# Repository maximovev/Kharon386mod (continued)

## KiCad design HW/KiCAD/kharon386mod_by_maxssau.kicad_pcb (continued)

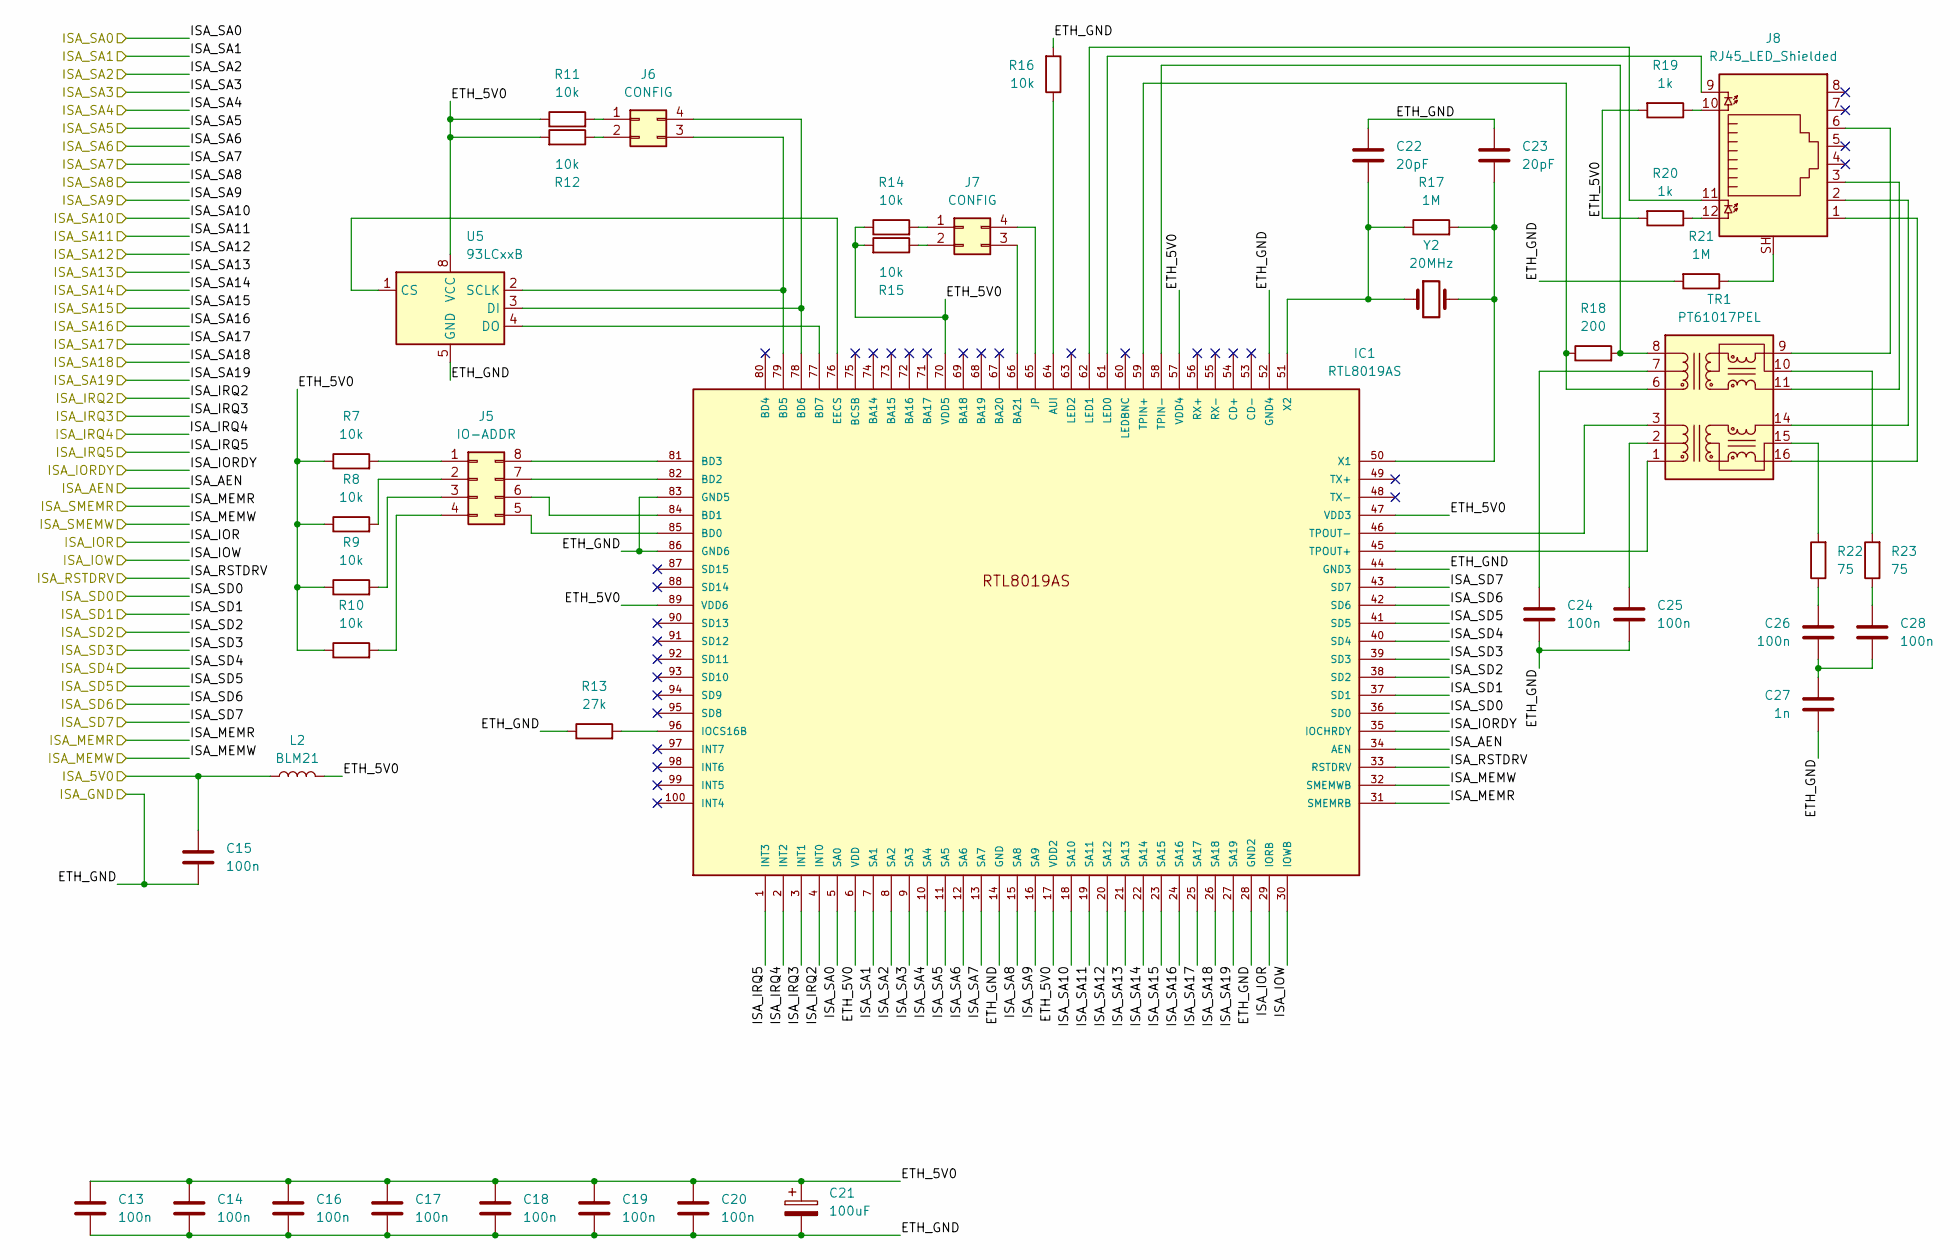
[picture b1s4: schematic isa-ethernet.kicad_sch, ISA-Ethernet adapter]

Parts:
C13, C14, C15, C16, C17, C18, C19, C20, C24, C25, C26, C28: 100n; C_0805_2012Metric_Pad1.18x1.45mm_HandSolder
C21: 100uF; CP_Elec_6.3x5.9
C22, C23: 20pF; C_0805_2012Metric_Pad1.18x1.45mm_HandSolder
C27: 1n; C_0805_2012Metric_Pad1.18x1.45mm_HandSolder
IC1: RTL8019AS
J5: IO-ADDR; PinHeader_2x04_P2.54mm_Vertical
J6, J7: CONFIG; PinHeader_2x02_P2.54mm_Vertical
J8: RJ45_LED_Shielded; RJ45_Cetus_J1B1211CCD_Horizontal
L2: BLM21; L_1210_3225Metric_Pad1.42x2.65mm_HandSolder
R7, R8, R9, R10, R11, R12, R14, R15, R16: 10k; R_0805_2012Metric_Pad1.20x1.40mm_HandSolder
R13: 27k; R_0805_2012Metric_Pad1.20x1.40mm_HandSolder
R17, R21: 1M; R_0805_2012Metric_Pad1.20x1.40mm_HandSolder
R18: 200; R_0805_2012Metric_Pad1.20x1.40mm_HandSolder
R19, R20: 1k; R_0805_2012Metric_Pad1.20x1.40mm_HandSolder
R22, R23: 75; R_0805_2012Metric_Pad1.20x1.40mm_HandSolder
TR1: PT61017PEL; Transformer_Ethernet_Bourns_PT61017PEL
U5: 93LCxxB; SOIC-8_3.9x4.9mm_P1.27mm
Y2: 20MHz; Crystal_HC49-U_Vertical

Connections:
/B_ISA_5V0: C15.1, L2.1; also elsewhere on the board
/B_ISA_A0: IC1.5 (SA0); also elsewhere on the board
/B_ISA_A1: IC1.7 (SA1); also elsewhere on the board
/B_ISA_A2: IC1.8 (SA2); also elsewhere on the board
/B_ISA_A3: IC1.9 (SA3); also elsewhere on the board
/B_ISA_A4: IC1.10 (SA4); also elsewhere on the board
/B_ISA_A5: IC1.11 (SA5); also elsewhere on the board
/B_ISA_A6: IC1.12 (SA6); also elsewhere on the board
/B_ISA_A7: IC1.13 (SA7); also elsewhere on the board
/B_ISA_A8: IC1.15 (SA8); also elsewhere on the board
/B_ISA_A9: IC1.16 (SA9); also elsewhere on the board
/B_ISA_A10: IC1.18 (SA10); also elsewhere on the board
/B_ISA_A11: IC1.19 (SA11); also elsewhere on the board
/B_ISA_A12: IC1.20 (SA12); also elsewhere on the board
/B_ISA_A13: IC1.21 (SA13); also elsewhere on the board
/B_ISA_A14: IC1.22 (SA14); also elsewhere on the board
/B_ISA_A15: IC1.23 (SA15); also elsewhere on the board
/B_ISA_A16: IC1.24 (SA16); also elsewhere on the board
/B_ISA_A17: IC1.25 (SA17); also elsewhere on the board
/B_ISA_A18: IC1.26 (SA18); also elsewhere on the board
/B_ISA_A19: IC1.27 (SA19); also elsewhere on the board
/B_ISA_AEN: IC1.34 (AEN); also elsewhere on the board
/B_ISA_D0: IC1.36 (SD0); also elsewhere on the board
/B_ISA_D1: IC1.37 (SD1); also elsewhere on the board
/B_ISA_D2: IC1.38 (SD2); also elsewhere on the board
/B_ISA_D3: IC1.39 (SD3); also elsewhere on the board
/B_ISA_D4: IC1.40 (SD4); also elsewhere on the board
/B_ISA_D5: IC1.41 (SD5); also elsewhere on the board
/B_ISA_D6: IC1.42 (SD6); also elsewhere on the board
/B_ISA_D7: IC1.43 (SD7); also elsewhere on the board
/B_ISA_IOR: IC1.29 (IORB); also elsewhere on the board
/B_ISA_IORDY: IC1.35 (IOCHRDY); also elsewhere on the board
/B_ISA_IOW: IC1.30 (IOWB); also elsewhere on the board
/B_ISA_IRQ3: IC1.3 (INT1); also elsewhere on the board
/B_ISA_IRQ4: IC1.2 (INT2); also elsewhere on the board
/B_ISA_IRQ5: IC1.1 (INT3); also elsewhere on the board
/B_ISA_IRQ9: IC1.4 (INT0); also elsewhere on the board
/B_ISA_RSTDRV: IC1.33 (RSTDRV); also elsewhere on the board
/B_ISA_SMEMR: IC1.31 (SMEMRB); also elsewhere on the board
/B_ISA_SMEMW: IC1.32 (SMEMWB); also elsewhere on the board
/isa-ethernet/ETH_5V0: C13.1, C14.1, C16.1, C17.1, C18.1, C19.1, C20.1, C21.1, IC1.6 (VDD), IC1.17 (VDD2), IC1.47 (VDD3), IC1.57 (VDD4), IC1.70 (VDD5), IC1.89 (VDD6), L2.2, R7.1, R8.1, R9.1, R10.1, R11.1, R12.2, R14.1, R15.2, R19.2, R20.2, U5.8 (VCC)
GND: C13.2, C14.2, C15.2, C16.2, C17.2, C18.2, C19.2, C20.2, C21.2, C22.2, C23.2, C24.2, C25.2, C27.2, IC1.14 (GND), IC1.28 (GND2), IC1.44 (GND3), IC1.52 (GND4), IC1.83 (GND5), IC1.86 (GND6), R13.1, R16.2, R21.2, U5.5 (GND); also elsewhere on the board
unnamed: C26.1, R22.1
unnamed: C26.2, C27.1, C28.2
unnamed: C28.1, R23.1
unnamed: IC1.64 (AUI), R16.1
unnamed: IC1.66 (BA21), J7.3
unnamed: IC1.85 (BD0), J5.5
unnamed: IC1.84 (BD1), J5.6
unnamed: IC1.82 (BD2), J5.7
unnamed: IC1.81 (BD3), J5.8
unnamed: IC1.79 (BD5), J6.3, U5.2 (SCLK)
unnamed: IC1.78 (BD6), J6.4, U5.3 (DI)
unnamed: IC1.77 (BD7), U5.4 (DO)
unnamed: IC1.76 (EECS), U5.1 (CS)
unnamed: IC1.96 (IOCS16B), R13.2
unnamed: IC1.65 (JP), J7.4
unnamed: IC1.61 (LED0), J8.9
unnamed: IC1.62 (LED1), J8.11
unnamed: IC1.59 (TPIN+), R18.1, TR1.6 (RD+)
unnamed: IC1.58 (TPIN-), R18.2, TR1.8 (RD-)
unnamed: IC1.45 (TPOUT+), TR1.1 (TD+)
unnamed: IC1.46 (TPOUT-), TR1.3 (TD-)
unnamed: C23.1, IC1.50 (X1), R17.2, Y2.2
unnamed: C22.1, IC1.51 (X2), R17.1, Y2.1
unnamed: J5.1, R7.2
unnamed: J5.2, R8.2
unnamed: J5.3, R9.2
unnamed: J5.4, R10.2
unnamed: J6.1, R11.2
unnamed: J6.2, R12.1
unnamed: J7.1, R14.2
unnamed: J7.2, R15.1
unnamed: J8.10, R19.1
unnamed: J8.12, R20.1
unnamed: J8.SH, R21.1
unnamed: C24.1, TR1.7 (C_RD)
unnamed: R23.2, TR1.10 (C_RX)
unnamed: C25.1, TR1.2 (C_TD)
unnamed: R22.2, TR1.15 (C_TX)
unnamed: J8.3, TR1.11 (RX+)
unnamed: J8.6, TR1.9 (RX-)
unnamed: J8.1, TR1.16 (TX+)
unnamed: J8.2, TR1.14 (TX-)

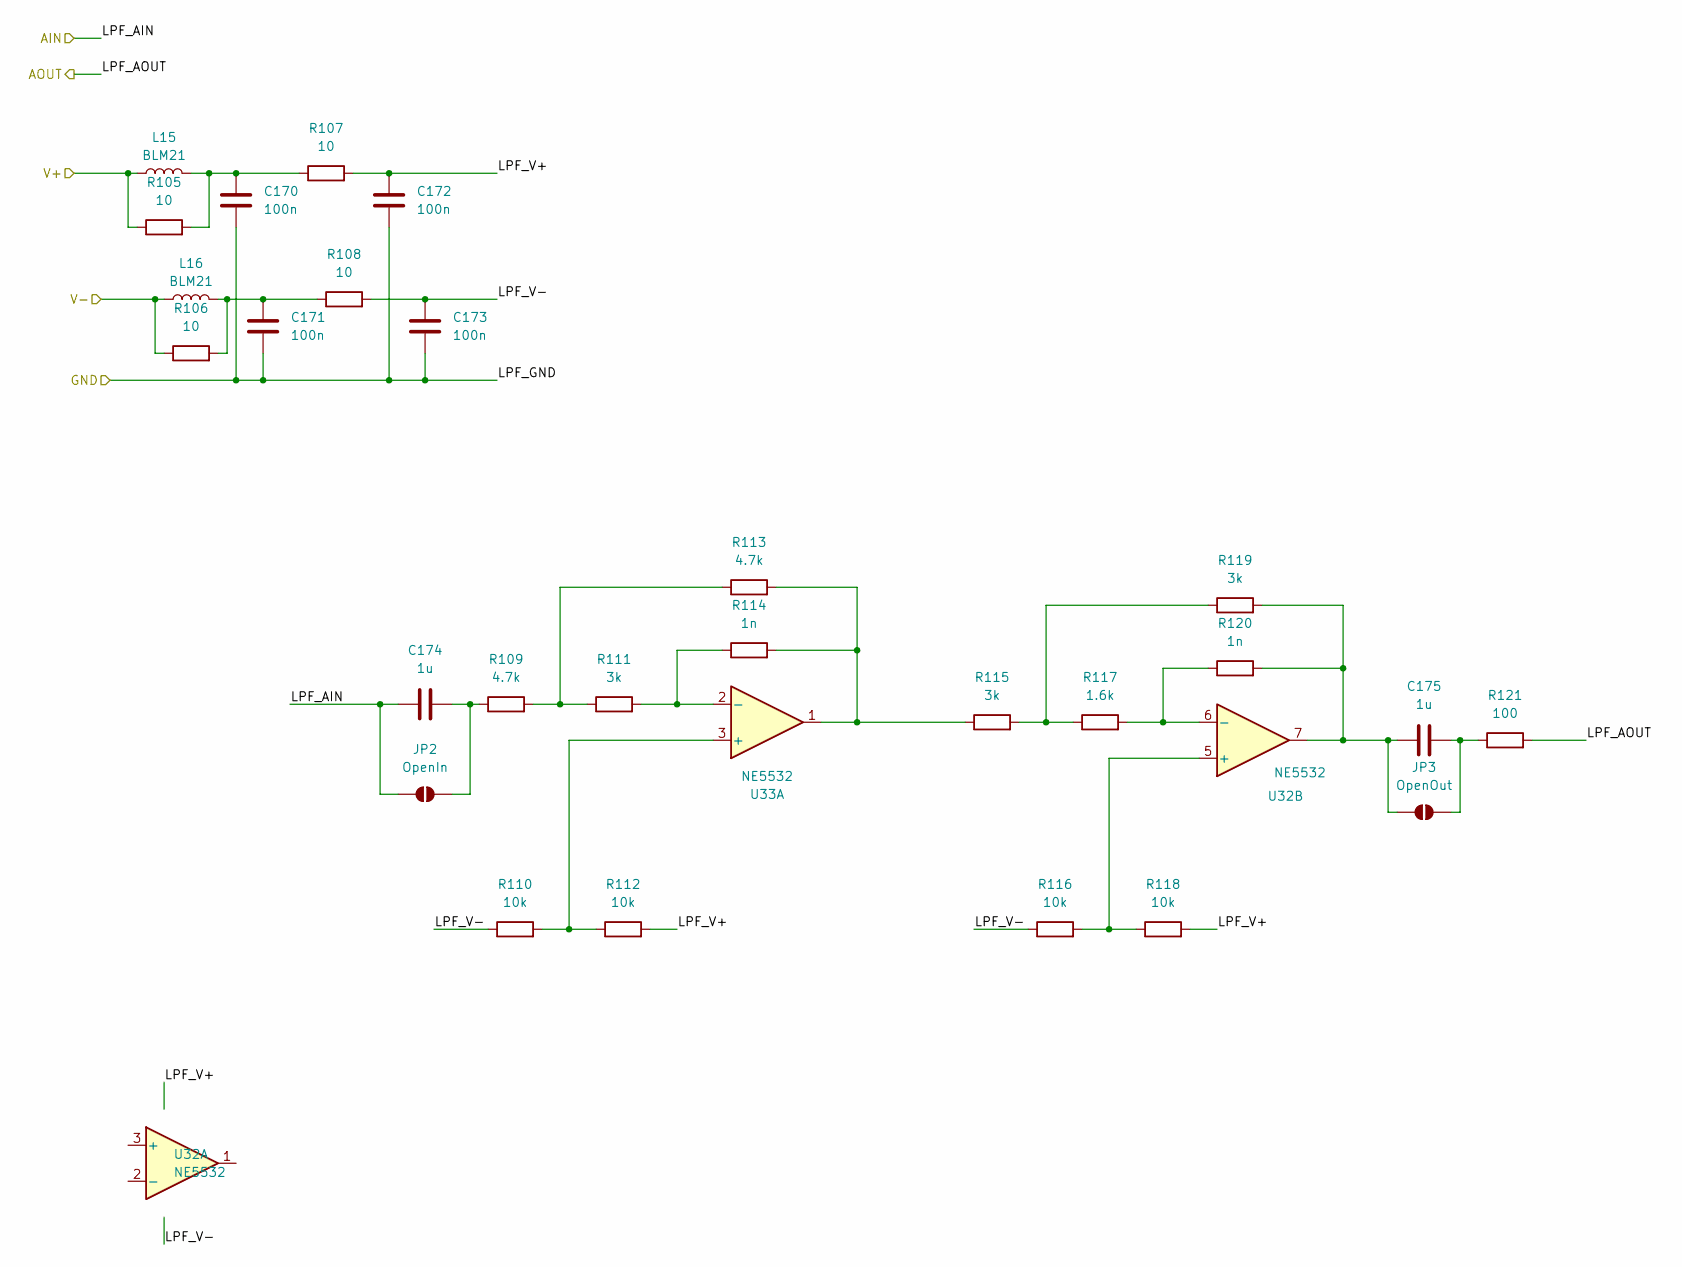
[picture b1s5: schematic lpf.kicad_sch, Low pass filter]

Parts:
C170, C171, C172, C173: 100n; C_0805_2012Metric_Pad1.18x1.45mm_HandSolder
C174, C175: 1u; C_Rect_L7.0mm_W2.5mm_P5.00mm
JP2: OpenIn; SolderJumper-2_P1.3mm_Open_TrianglePad1.0x1.5mm
JP3: OpenOut; SolderJumper-2_P1.3mm_Open_TrianglePad1.0x1.5mm
L15, L16: BLM21; L_0805_2012Metric_Pad1.15x1.40mm_HandSolder
R105, R106, R107, R108: 10; R_0805_2012Metric_Pad1.20x1.40mm_HandSolder
R109, R113: 4.7k; R_0805_2012Metric_Pad1.20x1.40mm_HandSolder
R110, R112, R116, R118: 10k; R_0805_2012Metric_Pad1.20x1.40mm_HandSolder
R111, R115, R119: 3k; R_0805_2012Metric_Pad1.20x1.40mm_HandSolder
R114, R120: 1n; R_0805_2012Metric_Pad1.20x1.40mm_HandSolder
R117: 1.6k; R_0805_2012Metric_Pad1.20x1.40mm_HandSolder
R121: 100; R_0805_2012Metric_Pad1.20x1.40mm_HandSolder
U32, U33: NE5532; SOIC-8_3.9x4.9mm_P1.27mm

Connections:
-12V: L16.1, R106.1; also elsewhere on the board
/ISA_VGA_SB/AVDD_OP: L15.1, R105.1; also elsewhere on the board
/ISA_VGA_SB/LPF1/LPF_V+: U32.8 (V+); also elsewhere on the board
/ISA_VGA_SB/LPF1/LPF_V-: U32.4 (V-); also elsewhere on the board
/ISA_VGA_SB/LPF2/LPF_V+: U33.8 (V+); also elsewhere on the board
/ISA_VGA_SB/LPF2/LPF_V-: U33.4 (V-); also elsewhere on the board
/ISA_VGA_SB/LPF/LPF_AIN: C174.1, JP2.1 (A); also elsewhere on the board
/ISA_VGA_SB/LPF/LPF_V+: C172.1, R107.2, R112.2, R118.2
/ISA_VGA_SB/LPF/LPF_V-: C173.1, R108.2, R110.1, R116.1
/ISA_VGA_SB/MIDI_L: R121.2; also elsewhere on the board
GND: C170.2, C171.2, C172.2, C173.2; also elsewhere on the board
unnamed: C170.1, L15.2, R105.2, R107.1
unnamed: C171.1, L16.2, R106.2, R108.1
unnamed: C174.2, JP2.2 (B), R109.1
unnamed: C175.1, JP3.1 (A), R119.2, R120.2, U32.7
unnamed: C175.2, JP3.2 (B), R121.1
unnamed 333: U33.7; also elsewhere on the board
unnamed: R109.2, R111.1, R113.1
unnamed: R113.2, R114.2, R115.1, U33.1
unnamed: R115.2, R117.1, R119.1
unnamed: R116.2, R118.1, U32.5 (+)
unnamed: R117.2, R120.1, U32.6 (-)
unnamed: R110.2, R112.1, U33.3 (+)
unnamed: R111.2, R114.1, U33.2 (-)
unnamed 428: U33.5 (+); also elsewhere on the board
unnamed 429: U33.6 (-); also elsewhere on the board

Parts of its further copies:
C176, C177, C178, C179, C182, C183, C184, C185, C188, C189, C190, C191: 100n; C_0805_2012Metric_Pad1.18x1.45mm_HandSolder
C180, C181, C186, C187, C192, C193: 1u; C_Rect_L7.0mm_W2.5mm_P5.00mm
JP4, JP6, JP8: OpenIn; SolderJumper-2_P1.3mm_Open_TrianglePad1.0x1.5mm
JP5, JP7, JP9: OpenOut; SolderJumper-2_P1.3mm_Open_TrianglePad1.0x1.5mm
L17, L18, L19, L20, L21, L22: BLM21; L_0805_2012Metric_Pad1.15x1.40mm_HandSolder
R122, R123, R124, R125, R139, R140, R141, R142, R156, R157, R158, R159: 10; R_0805_2012Metric_Pad1.20x1.40mm_HandSolder
R126, R130, R143, R147, R160, R164: 4.7k; R_0805_2012Metric_Pad1.20x1.40mm_HandSolder
R127, R129, R133, R135, R144, R146, R150, R152, R161, R163, R167, R169: 10k; R_0805_2012Metric_Pad1.20x1.40mm_HandSolder
R128, R132, R136, R145, R149, R153, R162, R166, R170: 3k; R_0805_2012Metric_Pad1.20x1.40mm_HandSolder
R131, R137, R148, R154, R165, R171: 1n; R_0805_2012Metric_Pad1.20x1.40mm_HandSolder
R134, R151, R168: 1.6k; R_0805_2012Metric_Pad1.20x1.40mm_HandSolder
R138, R155, R172: 100; R_0805_2012Metric_Pad1.20x1.40mm_HandSolder
U34: NE5532; SOIC-8_3.9x4.9mm_P1.27mm

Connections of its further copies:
-12V: L18.1, L20.1, L22.1, R123.1, R140.1, R157.1; also elsewhere on the board
/ISA_VGA_SB/AVDD_OP: L17.1, L19.1, L21.1, R122.1, R139.1, R156.1; also elsewhere on the board
/ISA_VGA_SB/LPF1/LPF_AIN: C180.1, JP4.1 (A); also elsewhere on the board
/ISA_VGA_SB/LPF1/LPF_V+: C178.1, R124.2, R129.2, R135.2; also elsewhere on the board
/ISA_VGA_SB/LPF1/LPF_V-: C179.1, R125.2, R127.1, R133.1; also elsewhere on the board
/ISA_VGA_SB/LPF2/LPF_AIN: C186.1, JP6.1 (A); also elsewhere on the board
/ISA_VGA_SB/LPF2/LPF_V+: C184.1, R141.2, R146.2, R152.2; also elsewhere on the board
/ISA_VGA_SB/LPF2/LPF_V-: C185.1, R142.2, R144.1, R150.1; also elsewhere on the board
/ISA_VGA_SB/LPF3/LPF_AIN: C192.1, JP8.1 (A); also elsewhere on the board
/ISA_VGA_SB/LPF3/LPF_V+: C190.1, R158.2, R163.2, R169.2, U34.8 (V+)
/ISA_VGA_SB/LPF3/LPF_V-: C191.1, R159.2, R161.1, R167.1, U34.4 (V-)
/ISA_VGA_SB/MIDI_R: R138.2; also elsewhere on the board
/ISA_VGA_SB/SB_OUT_L: R155.2; also elsewhere on the board
/ISA_VGA_SB/SB_OUT_R: R172.2; also elsewhere on the board
GND: C176.2, C177.2, C178.2, C179.2, C182.2, C183.2, C184.2, C185.2, C188.2, C189.2, C190.2, C191.2; also elsewhere on the board
unnamed: C176.1, L17.2, R122.2, R124.1
unnamed: C177.1, L18.2, R123.2, R125.1
unnamed: C182.1, L19.2, R139.2, R141.1
unnamed: C183.1, L20.2, R140.2, R142.1
unnamed: C188.1, L21.2, R156.2, R158.1
unnamed: C189.1, L22.2, R157.2, R159.1
unnamed: C180.2, JP4.2 (B), R126.1
unnamed 333: C181.1, JP5.1 (A), R136.2, R137.2; also elsewhere on the board
unnamed: C181.2, JP5.2 (B), R138.1
unnamed: C186.2, JP6.2 (B), R143.1
unnamed: C187.1, JP7.1 (A), R153.2, R154.2, U34.7
unnamed: C187.2, JP7.2 (B), R155.1
unnamed: C192.2, JP8.2 (B), R160.1
unnamed 339: C193.1, JP9.1 (A), R170.2, R171.2; also elsewhere on the board
unnamed: C193.2, JP9.2 (B), R172.1
unnamed: R126.2, R128.1, R130.1
unnamed: R130.2, R131.2, R132.1, U34.1
unnamed: R132.2, R134.1, R136.1
unnamed: R143.2, R145.1, R147.1
unnamed 356: R147.2, R148.2, R149.1; also elsewhere on the board
unnamed: R149.2, R151.1, R153.1
unnamed: R160.2, R162.1, R164.1
unnamed 359: R164.2, R165.2, R166.1; also elsewhere on the board
unnamed: R166.2, R168.1, R170.1
unnamed 428: R133.2, R135.1; also elsewhere on the board
unnamed 429: R134.2, R137.1; also elsewhere on the board
unnamed: R127.2, R129.1, U34.3 (+)
unnamed: R128.2, R131.1, U34.2 (-)
unnamed: R150.2, R152.1, U34.5 (+)
unnamed: R151.2, R154.1, U34.6 (-)
unnamed 434: R144.2, R146.1; also elsewhere on the board
unnamed 435: R145.2, R148.1; also elsewhere on the board
unnamed 436: R167.2, R169.1; also elsewhere on the board
unnamed 437: R168.2, R171.1; also elsewhere on the board
unnamed 438: R161.2, R163.1; also elsewhere on the board
unnamed 439: R162.2, R165.1; also elsewhere on the board

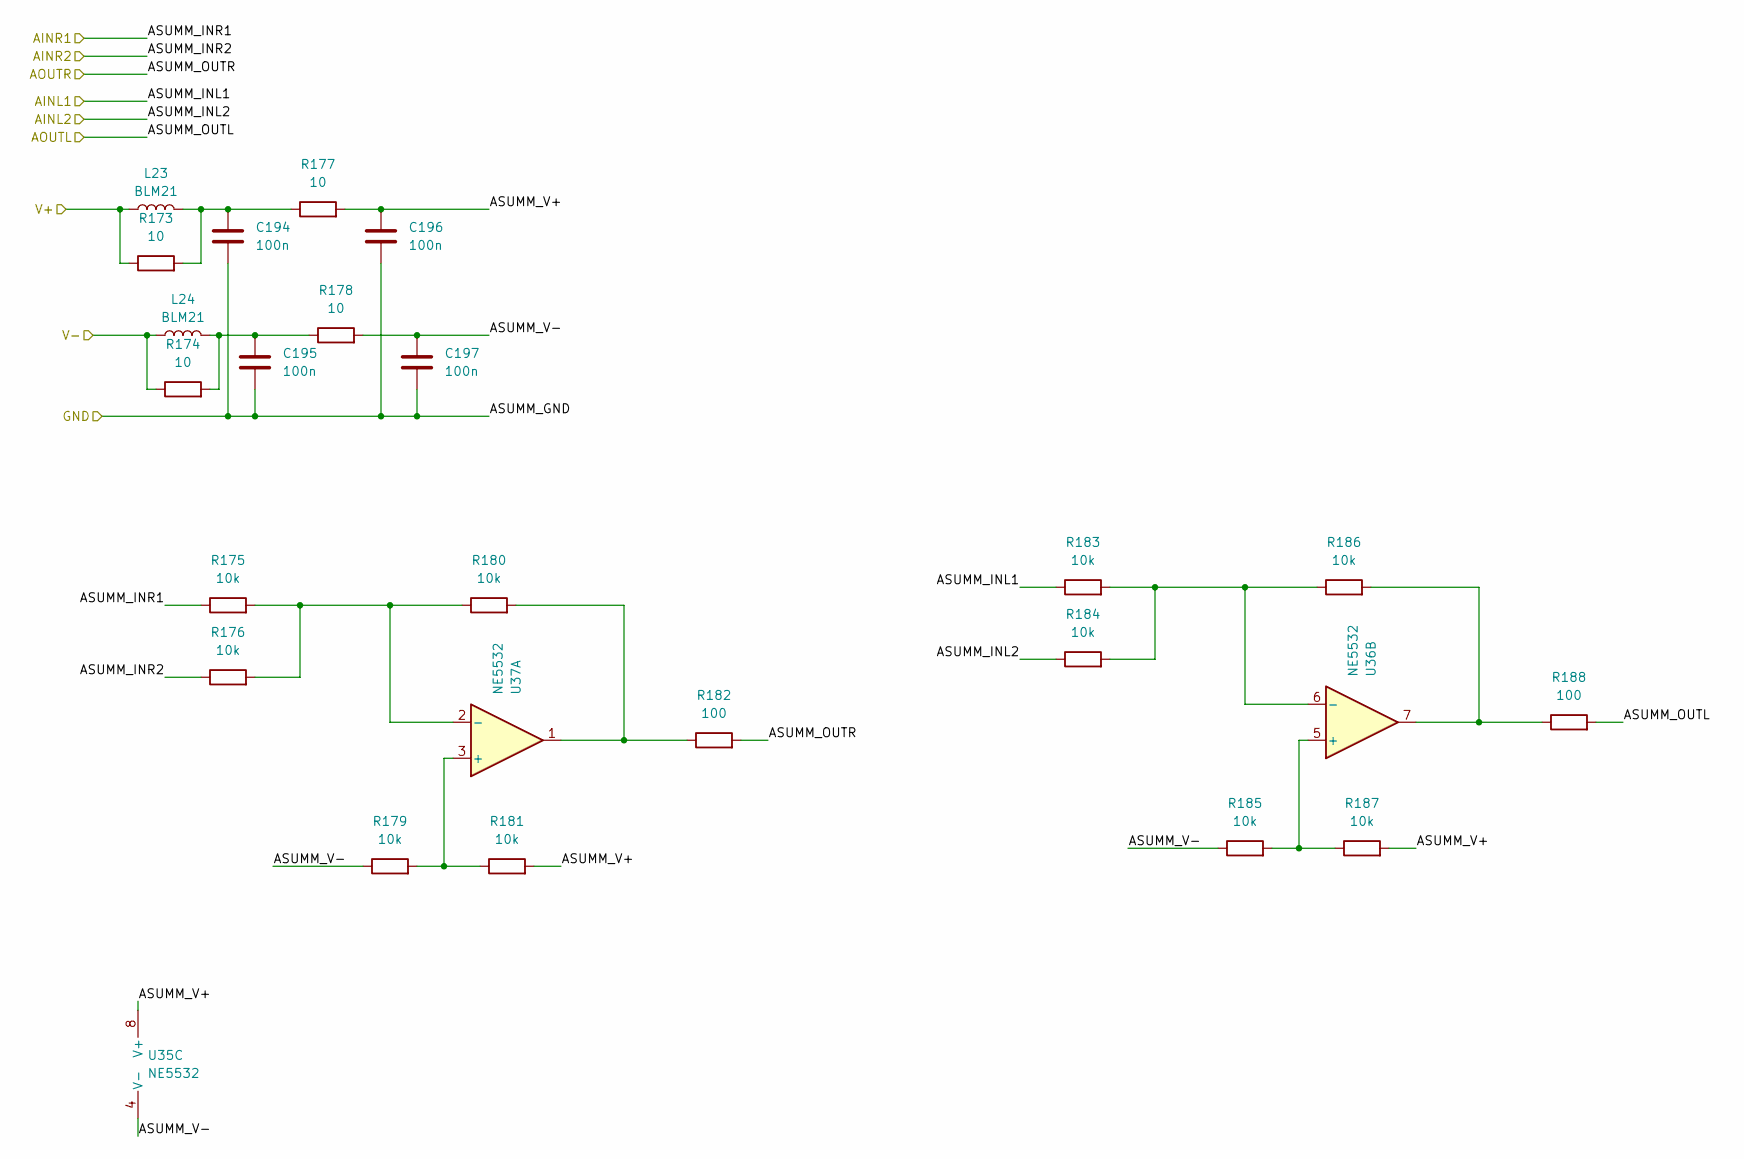
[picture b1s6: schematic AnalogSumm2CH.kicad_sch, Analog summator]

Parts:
C194, C195, C196, C197: 100n; C_0805_2012Metric_Pad1.18x1.45mm_HandSolder
L23, L24: BLM21; L_0805_2012Metric_Pad1.15x1.40mm_HandSolder
R173, R174, R177, R178: 10; R_0805_2012Metric_Pad1.20x1.40mm_HandSolder
R175, R176, R179, R180, R181, R183, R184, R185, R186, R187: 10k; R_0805_2012Metric_Pad1.20x1.40mm_HandSolder
R182, R188: 100; R_0805_2012Metric_Pad1.20x1.40mm_HandSolder
U35, U36, U37: NE5532; SOIC-8_3.9x4.9mm_P1.27mm

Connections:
-12V: L24.1, R174.1; also elsewhere on the board
/ISA_VGA_SB/AVDD_OP: L23.1, R173.1; also elsewhere on the board
/ISA_VGA_SB/AnalogSumm2CH/ASUMM_OUTL: R188.2; also elsewhere on the board
/ISA_VGA_SB/AnalogSumm2CH/ASUMM_OUTR: R182.2; also elsewhere on the board
/ISA_VGA_SB/AnalogSumm2CH/ASUMM_V+: C196.1, R177.2, R181.2, R187.2, U35.8 (V+)
/ISA_VGA_SB/AnalogSumm2CH/ASUMM_V-: C197.1, R178.2, R179.1, R185.1, U35.4 (V-)
/ISA_VGA_SB/MIDI_L: R184.1; also elsewhere on the board
/ISA_VGA_SB/MIDI_R: R176.1; also elsewhere on the board
/ISA_VGA_SB/SB_OUT_L: R183.1; also elsewhere on the board
/ISA_VGA_SB/SB_OUT_R: R175.1; also elsewhere on the board
GND: C194.2, C195.2, C196.2, C197.2; also elsewhere on the board
unnamed: C194.1, L23.2, R173.2, R177.1
unnamed: C195.1, L24.2, R174.2, R178.1
unnamed: R180.2, R182.1, U37.1
unnamed: R186.2, R188.1, U36.7
unnamed: R185.2, R187.1, U36.5 (+)
unnamed: R183.2, R184.2, R186.1, U36.6 (-)
unnamed: R179.2, R181.1, U37.3 (+)
unnamed: R175.2, R176.2, R180.1, U37.2 (-)

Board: 4 copper layers, 518 parts (0 on the bottom side), 440 nets, no tracks yet.

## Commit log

2026-01-08 first edits
2026-01-08 some edit
2026-01-09 pcb edit
2026-01-15 add LPF
2026-01-16 some eidts, remove com
2026-01-23 some edits, add HP amp
